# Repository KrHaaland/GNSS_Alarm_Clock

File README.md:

# GNSS Alarm Clock — Firmware

Firmware for the custom **SAMD51** alarm-clock board (Adafruit Metro M4
compatible), designed in `HARDWARE/` (KiCad). Two board revisions share one
firmware:

- **v2 (current)** — SAMD51J20A, **nPM1300 PMIC** with Li-ion charging and
  USB-C, LM3671 3.3 V + TPS61023 5 V boost, battery-backed RTC, MCU core on
  its internal buck regulator. See
  [`HARDWARE_V2.md`](HARDWARE_V2.md) and [ADR-0014](docs/adr/0014-npm1300-power-management.md)/[0015](docs/adr/0015-j20-default-swd-flashing.md).
  Default build: `metro_m4_j20`.
- **v1 (prototype)** — SAMD51J19A, LTC3226 + supercaps (design in
  `HARDWARE_OLD/`). Build: `adafruit_metro_m4`. The firmware detects the
  PMIC at runtime and degrades gracefully either way.

Time is set automatically from GNSS, the timezone (with DST) is derived offline
from the GNSS coordinates and saved to flash so it stays correct indoors, and
alarms drive an LED light-show + a tune through a class-D amp. The UI is LVGL on
a 428×142 color TFT driven by four buttons.

> **Current state:** firmware is feature-complete and running on hardware —
> display, GNSS time/timezone, alarms, audio, tunes-over-USB, settings, modes
> (speedometer/altimeter/USB-gamepad) and the RV-3028 RTC (hand-fitted; it was
> missing from the prototype) all work. See [`STATUS.md`](STATUS.md) and
> [`HARDWARE_REVIEW.md`](HARDWARE_REVIEW.md).

## Documentation

- **[User guide](docs/USER_GUIDE.md)** — buttons, menu, alarms, modes, tunes
- **[Architecture decisions](docs/adr/)** — why things are the way they are
- **[STATUS.md](STATUS.md)** — living status report · **[HARDWARE_REVIEW.md](HARDWARE_REVIEW.md)** — board findings
- **[HARDWARE_V2.md](HARDWARE_V2.md)** — v2 board reference (pinout, power tree, gotchas) · **[docs/sessions/](docs/sessions/)** — bench-session logs
- CI: GitHub Actions builds all firmware targets + runs the native test suite on every push

## What it does

- **Time**: The Quectel **L86** GNSS receiver (Serial1, 9600 NMEA, RMC+GGA @1 Hz
  plus GSV satellites-in-view every 5 s for the Sky-view screen, TinyGPS++ +
  a small in-house GSV parser) provides UTC. The clock is a `millis()`-anchored UTC counter
  disciplined by GNSS (re-syncs hourly / on ≥2 s drift) and backed by the
  **RV-3028-C7** RTC (I²C 0x52), whose VBACKUP sits on the battery (v2; the
  v1 prototype used the supercap rail) so it holds time through power loss. On boot the clock starts from the RTC
  immediately and refines from GNSS when a fix is available. A cold-start guard
  rejects the L86's free-running "year-2080" date so garbage can't be written
  into the backup RTC.
- **Timezone from coordinates**: An embedded **offline** lookup (213-box table
  covering every UTC zone worldwide — multi-zone countries split by region, plus
  no-DST exceptions like Arizona / Saskatchewan / Queensland / Kaliningrad;
  borders like US-zones and Afghanistan/Pakistan/India aligned to the real
  meridians). **Polygon zones** are checked before the boxes: real IANA
  timezone borders generated from timezone-boundary-builder data by
  `tools/gen_tz_polys.py` (tunable resolution/flash budget; enclaves ordered
  first), refinable by hand in `tools/tz_polygon_editor.html` (map GUI:
  draw/edit vertices, probe a point, export the header). Two resolutions,
  picked by flash size: v2/J20 gets the fine map
  (`src/TimezonePolyDataFine.h`, ~1–2 km borders, 404 zones / 56k vertices,
  ~250 KB), v1/J19 the coarse one (`src/TimezonePolyData.h`, ~57 KB). Anything not inside a polygon or box falls back
  to a whole-hour longitude estimate, so **every coordinate resolves**. Maps
  the GNSS position to a
  **POSIX TZ string with DST rules** (e.g. Oslo →
  `CET-1CEST,M3.5.0,M10.5.0/3`). The result is **persisted to internal flash**,
  so local time (including DST changes) stays correct after reboot even with no
  fix indoors. A DST-aware POSIX evaluator (`Timezone.*`, host-unit-tested)
  computes the offset. Manual zone override is available in the menu.
- **Alarms**: Two independent alarms with per-weekday masks. On trigger:
  - the **34 LEDs** (3 sections: left 10 / bottom 14 / right 10) run a chase at
    full brightness from a battery-capable rail (v2: TPS61023 5 V boost;
    v1: the LTC3226 supercap rail) — brightness never depends on the USB
    supply. The light show is **switchable per alarm** (Lights in the alarm
    editor; off = sound-only alarm),
  - a tune plays: a **WAV** from the QSPI flash drive, or one of 3 built-in
    melodies, via **DAC0 → TPA2016D2** class-D amp → speaker. WAVs pass a
    **200 Hz high-pass** in firmware: sub-bass cost the most battery current
    (speaker impedance minimum) for the least sound (ADR-0010),
  - optional **escalation**: after *N* minutes unacknowledged, the power buzzer
    joins in (v1 hardware only — v2 dropped the buzzer); auto-silence after
    30 min.
  - **Snooze**: short-press any button, or double-tap the clock (LIS3DH).
    **Stop**: long-press any button.
- **UI**: **LVGL 9.5** on an **NV3007 color TFT** (see below), driven by the 4
  buttons above the display: `[Back/Menu] [Prev/–] [Next/+] [OK]`. Screens:
  clock, menu, alarm-edit, time & zone, display, tunes, system-info,
  **sky view** (GSV polar plot + SNR bars — indoor antenna-placement aid),
  ringing. A true-black theme keeps the panel dark. Optional **starry night**:
  twinkling stars behind the clock digits between 22:00 and 06:00.
- **Modes** (Menu → Mode, cycles in place; alarms keep working in all of them):
  - **Alarm clock** — the normal HH:MM face.
  - **Speedometer** — the big figure shows GNSS ground speed in **km/h**.
  - **Altimeter** — GNSS altitude in **m** (MSL).
  - **Game mode** — the LIS3DH becomes a **USB HID gamepad**: tilt = stick
    X/Y, B2–B4 = buttons 1–3 (B1 keeps its menu role). The HID interface is
    always in the descriptor; it only sends reports in this mode.
- **Power (v2)**: the nPM1300 is driven end-to-end — input limit follows the
  USB-C CC advertisement (500 mA on PC ports, 1500 mA on real chargers,
  re-applied instantly on replug via the PMIC's IRQ line on PA04), charging
  400/800 mA to 4.10 V under an 80/70 °C die thermostat, live battery
  current on the Battery screen, a drawn SoC gauge on the clock face
  (ADR-0014/0016), and a low-battery policy: ship mode below 3.40 V (never
  during an alarm), fullscreen LOW BATTERY on a too-early wake, manual
  Shutdown in the menu — BUTTON1 or USB wakes it, the RTC keeps time
  throughout. The volume ceiling is bench-tuned to the PMIC's **1000 mA
  battery discharge limit (IBATLIM)** — exceeding it collapses VSYS and
  resets the device, so max volume (+7 dBV limiter) + LED chase stays under
  it with margin (ADR-0010/0014).
- **Tune upload**: the QSPI flash appears as a **USB flash drive** (`TUNES`) —
  drag & drop `.wav` files (PCM, 8/16-bit, mono/stereo, 8–48 kHz).

## Screenshots

Grabbed from the live firmware over USB serial (`tools/screenshot.py`).

| | |
|---|---|
|  |  |
| Clock face — battery gauge, charge bolt, alarm bell | Starry night (22:00–06:00) |
|  |  |
| First boot, no RTC/GNSS time yet | Sky view — GSV polar plot + SNR bars |
|  |  |
| Main menu | …scrolled |
|  |  |
| Speedometer mode (GNSS) | Altimeter mode (GNSS) |
|  |  |
| Game mode — USB HID gamepad | The 3D-printed enclosure |

## Display (NV3007)

The panel is an **NV3007 color TFT** (Newvision), native 142×428 bar type,
driven **landscape 428×142**. Driver: [`src/DisplayNV3007.cpp`](src/DisplayNV3007.cpp).
(The v1 prototype's ST7789 284×76 driver is kept in-tree — pick the panel via
**DISPLAY SELECT** in `platformio.ini`.)

- **Vendor init is mandatory**: `0xFF 0xA5` unlocks the extended register page
  (power/gamma/gate-driver/source-timing dump); without it the address engine
  wraps writes linearly across the glass. `0xFF 0x00` returns to the DCS page.
  Sequence cross-verified against five independent drivers (Arduino_GFX, LVGL
  lv_nv3007, vendor reference, STM32 + esp_lcd ports).
- GRAM is **168×428**; the 142 visible columns are inset 12/14. Landscape
  (`MADCTL 0xA0`, flipped 180° to match the enclosure mounting) puts the
  inset on RASET: **`NV_Y_OFFSET 12`** (unflipped 0x60 → 14). Inversion OFF.
- **SPI mode 0** (an NV3007 quirk — ST7789 setups often run mode 3), **30 MHz**
  (SERCOM2 re-clocked from the 120 MHz GCLK0 — the default 48 MHz source
  quantizes to 24 MHz max). Pixels stream via an **async DMA flush with double
  buffering** (ADR-0012, superseding ADR-0002's DMA ban): LVGL renders the
  next strip while the DMAC streams the previous one, and the completion IRQ
  hands the buffer back. Falls back to a synchronous DRE-paced register loop
  if the DMA channel is unavailable. Full frame ~26 ms on the wire, hidden
  behind rendering.
- Known silicon quirk: tiny partial writes can half-light adjacent pixels for
  RGB channel values 1–31 against black; LVGL's strip-sized flushes avoid it.
- Backlight D11/PA19, PWM-dimmed; shake-to-wake; `DISPLAY_SELFTEST` bring-up
  pattern test (colors/border/origin) as before.
- The clock figure uses a **generated 100 px Montserrat subset**
  (`src/font_clock_100.c`, 18 chars) — replacing the full 48 px font actually
  **shrank** flash by 67 KB (ADR-0011).

## Storage decision

The board has two candidate "EEPROMs" for tunes: the 24LC512 (64 KB, I²C) and a
QSPI serial flash. The firmware uses the **QSPI flash** (exposed as the USB
drive): far larger, faster, on the standard Metro M4 QSPI pins, and it enables
the drag-and-drop workflow.

**Settings** are packed into the **RV-3028 RTC's 43-byte user EEPROM**.
Chosen because it survives **firmware reflashes** (the old internal-flash
emulation sat inside the app image and was wiped on every update), takes
~100k writes/byte, and frees the **24LC512 to be dropped from the hardware-v2
BOM** (it still ACKs at 0x50 on v1 boards, unused). Verified on hardware:
settings survive both power cycles and reflashes.

### RTC user-EEPROM memory map (38 of 43 bytes)

Space is won by not storing derived data: TZ strings re-derive at boot from
the stored position (or the manual GMT-ladder index), and alarm tune filenames
are stored as 16-bit FNV-1a hashes re-matched against the TUNES directory
(missing file → builtin melody). Multi-byte fields are little-endian.

| Addr | Size | Field |
|---|---|---|
| `0x00` | 2 | Magic `'G' 'C'` |
| `0x02` | 1 | Pack-format version (4) — older blocks (v1–v3) migrate in place at boot, nothing is reset |
| `0x03` | 1 | Flags: b0 tzAuto, b1 tapSnooze, b2 use24h, b3 havePosition, b4–5 mode, b6 starryNight |
| `0x04` | 2 | Latitude, centidegrees (i16) |
| `0x06` | 2 | Longitude, centidegrees (i16) |
| `0x08` | 1 | Manual zone index into `TZ_TABLE` (`0xFF` = none/auto) |
| `0x09` | 1 | Volume (0–10) |
| `0x0A` | 1 | Snooze minutes |
| `0x0B` | 1 | Buzzer escalation after N min (0 = off) |
| `0x0C` | 1 | Brightness |
| `0x0D` | 2 | Dim timeout, seconds (u16) |
| `0x0F` | 1 | Dim brightness |
| `0x10` | 3 | Snooze counter, all time (u24, caps at 16.7 M) |
| `0x13` | 2 | Snooze counter, this week (u16) |
| `0x15` | 2 | Week start, local epoch-day − 18262 (u16, base 2020-01-01) |
| `0x17` | 7 | Alarm 1: flags (b0 enabled, b1–2 ramp Off/15/30/60 s, b3–4 random ±0/1/5/9 min, b5 lights-OFF — inverted so old blocks read as on), hour, minute, daysMask, melodyId, tuneHash (u16) |
| `0x1E` | 7 | Alarm 2: same layout |
| `0x25` | 1 | Checksum (block sums to `0xFF`) — **written last**, so a torn write invalidates the image |
| `0x26` | 5 | Free / future |

> **RV-3028 EEPROM quirks (bench-found, handled in `RtcRV3028.cpp`):** the
> chip **NACKs all I²C** while its EEPROM engine runs — both during the
> power-on auto-refresh (>100 ms) and in short windows after each programmed
> byte. The driver therefore treats failed STATUS reads as "still busy"
> (300 ms deadline), retries each byte transaction up to 5×, and read-back
> verifies every written byte.

> **Flash BOM note:** the schematic specifies a 4 MB Macronix MX25L3233F, but
> assembled boards carry a **16 MB Winbond W25Q128** (JEDEC 0xEF4018). The driver
> auto-detects the real chip via the library's default device list, so the true
> size is used for the USB drive.

## Pin map (from the KiCad netlist)

| Function | MCU pin | Arduino pin |
|---|---|---|
| Display CS / DC / RST / BL | PA18 / PA17 / PA16 / PA19 | D10 / D12 / D13 / D11 |
| Display SPI (SERCOM2) | PA12 MOSI, PA13 SCK | MOSI/SCK |
| GNSS L86 UART (SERCOM3) | PA22 TX → L86, PA23 RX ← L86 | Serial1 |
| GNSS FORCE_ON / RESET_N | PB00 / PB31 | direct port |
| I²C @100 kHz: RTC 0x52, amp 0x58, accel 0x18, EEPROM 0x50 | PB02 SDA, PB03 SCL | SDA/SCL |
| Buttons SW1..SW4 (L→R, active low) | PB14, PB13, PB12, PB15 | D5, D4, D7, D6 |
| LED gates: left / bottom / right | PA21 / PA20 / PA06 | D8 / D9 / A2 |
| Audio DAC → TPA2016 | PA02 (DAC0) | A0 |
| Amp ~SD (HIGH = on) | PB17 | D2 |
| Power buzzer gate (J5) | PB16 | D3 |
| Supercap CAPGOOD (LTC3226) | PA04 | A3 |
| LIS3DH INT1 (polled, unused) | PB08 | A4 |
| 24LC512 WP | PB01 | direct port |
| QSPI flash | PA08–11, PB10, PB11 | QSPI |

## Building & flashing

```sh
pio run                      # build (default env: adafruit_metro_m4)
pio test -e native           # host-side unit tests (timezone/DST engine)
```

### MCU select (J19 / J20)

The prototype has a **SAMD51J19A** (512 KB flash, ~95% full); the next revision
uses a **SAMD51J20A** (1 MB flash, ~48% — same pinout). Pick the build in
`platformio.ini` (`default_envs`) or per-invocation:

| env | MCU | notes |
|---|---|---|
| `adafruit_metro_m4` | J19A 512 KB | default (current prototype) |
| `metro_m4_j20` | J20A 1 MB | `boards/samd51j20a_metro.json` + `ld/samd51j20a_*.ld` |
| `sim` / `sim_j20` | either | + serial GNSS simulator (`-DGNSS_SIM`) |

```sh
pio run -e metro_m4_j20      # J20 build; flash .pio/build/metro_m4_j20/firmware.bin @0x4000
```

> **J20 + stock bootloader:** the Metro M4 UF2 bootloader is built for the
> J19A and reads the "stay in bootloader" magic at *its* RAM top
> (0x2002FFFC); a J20 app writes it at 0x2003FFFC, so the 1200-baud touch
> used to land straight back in the app. `tools/patch_tinyusb_power.py`
> patches the core's `initiateReset()` to write **both** addresses — USB
> uploads now work on the J20 with the stock bootloader.

Two flashing paths:

**A) USB (normal, no tools):** `pio run -e metro_m4_j20 -t upload` —
1200-baud touch into the bootloader, bossac writes + verifies at 0x4000
(~4 s). Manual alternative: double-tap RESET to mount the `METROM4BOOT`
drive and drag `firmware.uf2` onto it.

**B) SWD via Atmel-ICE (used in development):**

```sh
# build first, then flash the .bin at 0x4000 (offset preserves the bootloader)
openocd -c "adapter driver cmsis-dap" -c "transport select swd" \
        -c "adapter speed 2000" -f target/atsame5x.cfg \
        -c "init" -c "reset halt" \
        -c "flash write_image erase .pio/build/adafruit_metro_m4/firmware.bin 0x00004000 bin" \
        -c "reset run" -c "shutdown"
```

> ⚠️ **Never flash the `.elf` over SWD.** Its LOAD segment sits at address `0x0`
> and will overwrite the UF2 bootloader at flash start, bricking drag-and-drop
> programming (recovery = re-flash the bootloader). Always flash the **`.bin` at
> `0x4000`**. The bootloader region is additionally guarded by the
> **BOOTPROT fuse (16 KB)** since a brownout-induced wild NVMCTRL write once
> zeroed the bootloader's vector table (see `docs/sessions/`); clear it with
> `atsame5 bootloader 0` before intentional bootloader updates, restore with
> `atsame5 bootloader 16384`.

`pio device monitor -b 115200` opens the USB-CDC console. Sending `~` on
the console streams the next rendered frame as a screenshot —
`python3 tools/screenshot.py` grabs it and writes a PNG (used for the
documentation images; works on the live device, any screen).

### USB identity

The app enumerates as **`1209:0001` — "K. Haaland / GNSS Alarm Clock"**.
VID `0x1209` belongs to [pid.codes](https://pid.codes) (free USB IDs for
open-source hardware); `0x0001` is their official **test PID**, fine for
personal use — register a permanent PID via a pid.codes PR (requires a public,
OSI-licensed repo) before distributing hardware. Identity lives in
`boards/samd51j19a_kh.json` / `boards/samd51j20a_metro.json`. Bootloader mode
(double-tap reset) still enumerates as Adafruit `239A` until a custom
uf2-samdx1 is built.

### Simulated GNSS (`env:sim`)

To test the timezone/clock pipeline on-device **without a real fix**, build the
`sim` env — identical firmware plus `-DGNSS_SIM` (the L86 init is skipped and a
serial console feeds position/time):

```sh
pio run -e sim -t upload      # or SWD-flash .pio/build/sim/firmware.bin @0x4000
pio device monitor -b 115200
```

Then type commands into the monitor:

```
pos 59.91 10.75              set a fix; resolves + applies the timezone
tz  -33.87 151.2             query a zone (Jan/Jul offset + DST), no state change
utc 2026 7 13 12 0 0         set the UTC clock so local time shows on the display
status                       print fix / UTC / local time / zone
nofix                        drop the simulated fix
```

`pos` also updates the on-screen clock's zone immediately, so you can watch the
display follow you around the globe. The `sim` code compiles to nothing in the
normal build — zero production-flash cost.

## Source layout

| File | Responsibility |
|---|---|
| `src/main.cpp` | Boot order, super-loop, alarm ↔ UI ↔ button routing, I²C @100 kHz |
| `src/ClockKeeper.*` | UTC anchor, GNSS→RTC discipline, local time / DST |
| `src/Timezone.*` | Coord→zone polygons+boxes + POSIX TZ/DST evaluator (host-testable) |
| `src/TimezonePolyData.h` | Polygon zone data: `tools/gen_tz_polys.py` (world set) / `tools/tz_polygon_editor.html` (hand edits) |
| `src/Gnss.*` | L86 NMEA via TinyGPS++, PMTK config, position/speed/altitude |
| `src/RtcRV3028.*` | RV-3028-C7 driver wrapper (backup switchover, UTC, PORF) |
| `src/AlarmManager.*` | Trigger scan, ringing/snooze/escalation state machine |
| `src/AudioEngine.*` | TC2 ISR → DAC0 playback, WAV streaming, melodies, buzzer |
| `src/TuneStorage.*` | QSPI flash, FAT12 volume, USB mass storage |
| `src/DisplayST7789.*` | ST7789 driver + LVGL 9 flush (RGB565), bring-up self-test |
| `src/Ui.*` | LVGL screens: clock, menu, alarm edit, zone, display, tunes, info, sky view, battery, lights, ringing |
| `src/PmicNPM1300.*` | nPM1300: CC-based input limit, charger, IBAT/SoC, ship mode, IRQ (v2) |
| `src/Buttons.*` / `src/Leds.*` | Debounced input, LED section patterns |
| `src/AmpTPA2016.*` / `src/AccelLIS3DH.*` | Amp gain/enable, double-tap-to-snooze |
| `src/Settings.*` | Persistent settings packed into the RTC's user EEPROM (v4, 38 B) |
| `src/SimConsole.*` | Serial "virtual GPS" console — `env:sim` only (`-DGNSS_SIM`) |

## Diagnostics (compile-time, default off)

- `DISPLAY_SELFTEST` in [`DisplayST7789.cpp`](src/DisplayST7789.cpp) — on-glass
  pattern test (RGB fills, edge border) instead of LVGL.
- `I2C_SCAN` in [`main.cpp`](src/main.cpp) — loops scanning the I²C bus and
  prints ACKing addresses over USB serial (used to diagnose the RTC).

## Known issues / verify on hardware

See [`STATUS.md`](STATUS.md) for the full list. Highlights:

- 🔴 **RV-3028 RTC (U5) does not ACK on I²C** — bad joint / power on U5; being
  reflowed. (Time still works from GNSS; only power-off holdover is affected.)
- **L86 1PPS (pin 6) and AADET_N (pin 8) are unrouted** — no hardware PPS
  timing, no antenna-detect.
- **`CAPGOOD` polarity** assumed HIGH = charged (LTC3226 open-drain + pullup).
- Plus the schematic findings in [`HARDWARE_REVIEW.md`](HARDWARE_REVIEW.md)
  (LM3671 VIN/SW, L86 V_BCKP cold-start, D3 diode, C30, crystal caps, …).

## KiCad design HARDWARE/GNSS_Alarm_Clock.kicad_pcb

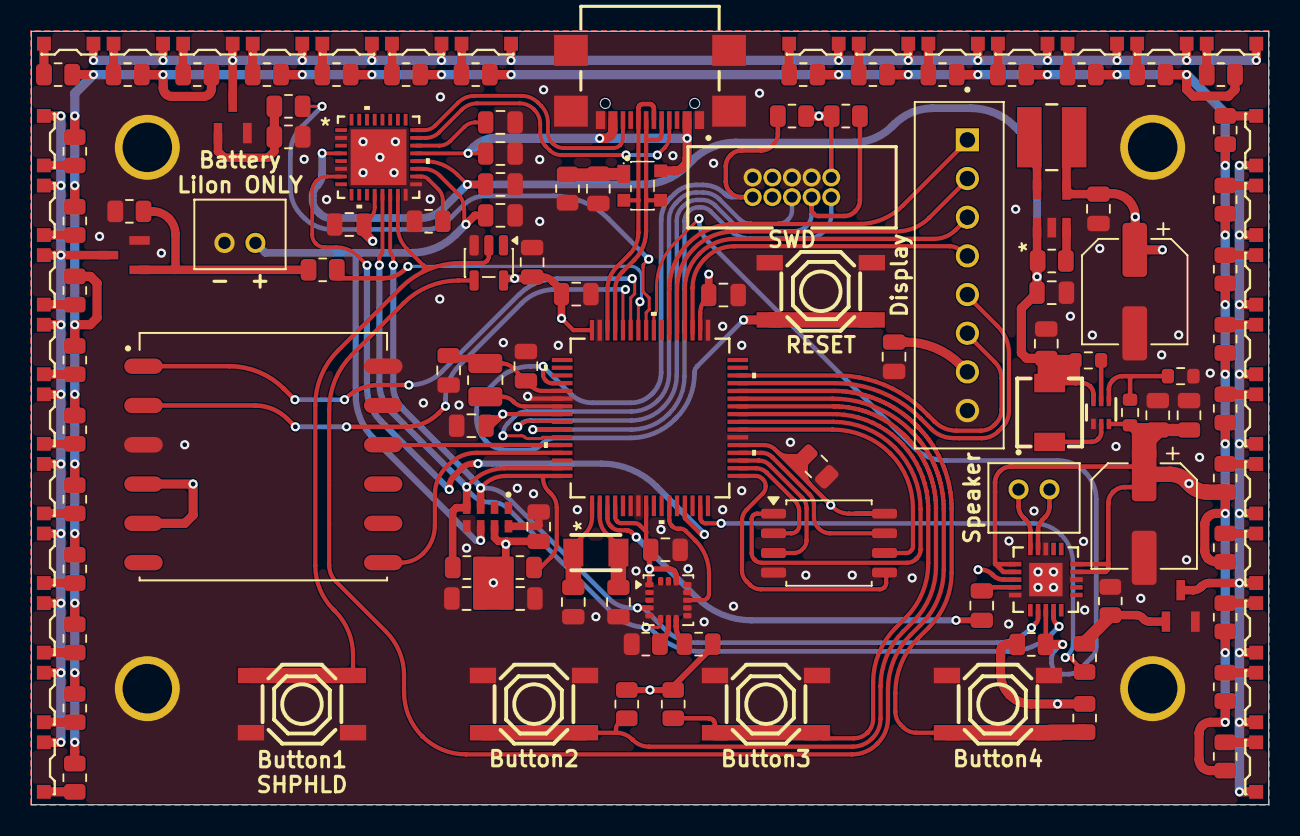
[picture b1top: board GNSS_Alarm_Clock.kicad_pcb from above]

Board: 4 copper layers, 80.0 x 50.0 mm, 146 parts (0 on the bottom side), 101 nets.

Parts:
C1, C3, C4: 22µF; C_0805_2012Metric
C2, C5, C26: 1uF; C_0805_2012Metric
C6, C7, C8, C9, C10, C11, C12, C16, C17, C19, C20, C22, C28: 10uF; C_0805_2012Metric
C13: 4.7uF; C_0805_2012Metric
C14, C15, C27: 100nF; C_0805_2012Metric
C18, C21: 220uF; CP_Elec_6.3x5.7
C24, C25: 10pF; C_0805_2012Metric
C29: 10μF; C_0805_2012Metric
J1: USB4110GFA; USB4110-GF-A
J3: SWD-Connector_3220-10-0100-00; SWD-Connector
J4: B8B-XH-A
J6, J7: B2B-PH-K-S
L1: 2.2uH; VLCF4020T-2R2N1R7
L2: 1µH; YXMAA0412-1R0M-ANP
L4: 10uH; L_1008_2520Metric
LED1, LED2, LED3, LED4, LED5, LED6, LED7, LED8, LED9, LED10, LED11, LED12, LED13, LED14, LED15, LED16, LED17, LED18, LED19, LED20, LED21, LED22, LED23, LED24, LED25, LED26, LED27, LED28, LED29, LED30, LED31, LED32, LED33, LED34: OR-PL020W
R1, R8, R9, R10: 1M; R_0805_2012Metric
R4, R12: 100KΩ; R_0603_1608Metric
R5: 732KΩ; R_0603_1608Metric
R6, R7: 4.7K; R_0805_2012Metric
R13: 100k; R_0805_2012Metric
R15, R54, R56: 470Ω; R_0805_2012Metric
R16: 10KΩ; R_0805_2012Metric
R18, R55, R57, R58, R63, R68: 10kΩ; R_0805_2012Metric
R20, R21, R22, R23, R24, R25, R26, R27, R28, R29, R30, R31, R32, R33, R34, R35, R36, R37, R38, R39, R40, R41, R42, R43, R44, R45, R46, R47, R48, R49, R50, R51, R52, R53: 80Ω; R_0805_2012Metric
R66: 1kΩ; R_0805_2012Metric
R67: 100kΩ; R_0805_2012Metric
SW1, SW2, SW3, SW4, SW5: TS-1187A-B-A-B
U1: TPA2016D2RTJR; TPA2016D2
U2: PRTR5V0U2X_C2827688; PRTR5V0U2X
U3: NPM1300-QEAA-R7; nPM1300
U4: L86-M33
U5: RV-3028-C7
U6: TPS61023DRLR; TPS61023
U7: LIS3DH; LGA-16_3x3mm_P0.5mm_LayoutBorder3x5y
U8: 25Q128; SOIC-8_5.3x5.3mm_P1.27mm
U9: 74LVC1G17; SOT-23-5
U10, U11, U12: IRLML6344TRPBF; IRLML6344
U14: LM3671MFX-3.3/NOPB; LM3671MFX-3.3
U18: ATSAMD51J19A-AUT; ATSAMD51J19_TQFP
X1: 32.768; Q13FC13500005

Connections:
+3.3V: C6.1, C7.1, C8.1, C9.1, C10.1, C11.1, C14.1, C15.1, C16.1, C17.1, C18.1, C20.1, C28.1, J3.1 (Vref), J4.7, L1.2, R6.2, R7.2, R8.1, R9.1, R10.1, R63.1, R66.2, R67.2, R68.2, U1.13 (AVDD), U3.12 (VDDIO), U4.4 (VCC), U4.5 (V_BCKP), U5.7 (VDD), U7.1 (VDD_IO), U7.14 (VDD), U8.8 (VCC), U9.5 (VCC), U14.4 (FB), U18.4 (PA03), U18.8 (VDDANA), U18.21 (VDDIOB), U18.34 (VDDIO), U18.48 (VDDIO), U18.56 (VDDIO)
+5V: C1.1, C4.1, C21.1, R5.1, R20.1, R21.1, R22.1, R23.1, R24.1, R25.1, R26.1, R27.1, R28.1, R29.1, R30.1, R31.1, R32.1, R33.1, R34.1, R35.1, R36.1, R37.1, R38.1, R39.1, R40.1, R41.1, R42.1, R43.1, R44.1, R45.1, R46.1, R47.1, R48.1, R49.1, R50.1, R51.1, R52.1, R53.1, U1.4 (PVDDL_2), U1.5 (PVDDL), U1.11 (PVDDR_2), U1.12 (PVDDR), U6.6 (VOUT)
AmpShutdown: R68.1, U1.18 (SDZ), U18.40 (D2/PB17)
Analog: C27.1, U18.3 (PA02/A0/PWM)
BUTTON1: U9.4, U18.27 (PB14/D5)
BUTTON2: R8.2, SW2.3, SW2.4, U18.26 (PB13/D4)
BUTTON3: R9.2, SW3.3, SW3.4, U18.25 (PB12/D7)
BUTTON4: R10.2, SW4.3, SW4.4, U18.28 (PB15/D6)
DISP_BL: J4.1, U18.38 (D11/PA19)
DISP_CS: J4.2, U18.37 (D10/PA18)
DISP_DC: J4.3, U18.36 (D12/PA17)
DISP_RST: J4.4, U18.35 (D13/PA16)
GND: C1.2, C2.2, C3.2, C4.2, C5.2, C6.2, C7.2, C8.2, C9.2, C10.2, C11.2, C12.2, C13.1, C14.2, C15.2, C16.2, C17.2, C18.2, C19.2, C20.2, C21.2, C22.2, C24.1, C25.1, C26.1, C28.2, C29.1, J1.A1/B12 (GND), J1.B1/A12 (GND__1), J1.S1 (GND__2), J1.S2 (GND__3), J1.S3 (GND__4), J1.S4 (GND__5), J3.3 (GND), J3.5 (GND), J3.9 (GND), J4.8, J7.2, R1.2, R12.2, R16.1, R18.1, R55.2, R57.2, R58.2, SW1.3, SW1.4, SW2.1, SW2.2, SW3.1, SW3.2, SW4.1, SW4.2, SW5.3, SW5.4, U1.3 (AGND), U1.8 (PGND), U1.15 (INR+), U1.21 (EP), U3.2 (PVSS1), U3.6 (PVSS2), U3.16 (VSET2), U3.17 (VSET1), U3.33 (AVSS), U4.3 (GND), U4.12 (GND), U5.5 (VSS), U5.8 (EVI), U6.4 (GND), U7.5 (GND), U7.10 (GND), U7.12 (GND), U8.4 (GND), U9.3 (GND), U10.2, U11.2, U12.2, U14.2 (GND), U18.7 (GNDANA), U18.22 (GND), U18.33 (GND), U18.47 (GND), U18.54 (GND)
GNSS_FOn: U4.7 (FORCE_ON), U18.61 (PB00)
GNSS_Reset: U4.10 (~RESET), U18.60 (PB31)
I2C_SCL: R7.1, U1.17 (SCL), U3.14 (SCL), U5.3 (SCL), U7.4 (SCL/SPC), U18.64 (SCL/PB03)
I2C_SDA: R6.1, U1.19 (SDA), U3.13 (SDA), U5.4 (SDA), U7.6 (SDA/SDI/SDO), U18.63 (SDA/PB02)
LIS3DH_INT1: U7.11 (INT1), U18.11 (PB08/A4)
LedsB-K: LED11.1 (-), LED12.1 (-), LED13.1 (-), LED14.1 (-), LED15.1 (-), LED16.1 (-), LED17.1 (-), LED18.1 (-), LED19.1 (-), LED20.1 (-), LED21.1 (-), LED22.1 (-), LED23.1 (-), LED24.1 (-), U11.3
LedsB-S: R54.1, U18.41 (D9/PA20)
LedsL-K: LED1.1 (-), LED2.1 (-), LED3.1 (-), LED4.1 (-), LED5.1 (-), LED6.1 (-), LED7.1 (-), LED8.1 (-), LED9.1 (-), LED10.1 (-), U10.3
LedsL-S: R15.1, U18.42 (D8/PA21)
LedsR-K: LED25.1 (-), LED26.1 (-), LED27.1 (-), LED28.1 (-), LED29.1 (-), LED30.1 (-), LED31.1 (-), LED32.1 (-), LED33.1 (-), LED34.1 (-), U12.3
LedsR-S: R56.1, U18.15 (PA06/A2)
McuRX: U4.2 (TXD1), U18.44 (RX/D0/PA23)
McuTX: U4.1 (RXD1), U18.43 (TX/D1/PA22)
unnamed: C2.1, R1.1, U2.1
unnamed: LED1.2 (+), R20.2
unnamed: LED2.2 (+), R21.2
unnamed: LED3.2 (+), R22.2
unnamed: LED4.2 (+), R23.2
unnamed: LED5.2 (+), R24.2
unnamed: LED6.2 (+), R25.2
unnamed: LED7.2 (+), R26.2
unnamed: LED8.2 (+), R27.2
unnamed: LED9.2 (+), R28.2
unnamed: LED10.2 (+), R29.2
unnamed: LED11.2 (+), R30.2
unnamed: LED12.2 (+), R31.2
unnamed: LED13.2 (+), R32.2
unnamed: LED14.2 (+), R33.2
unnamed: LED15.2 (+), R34.2
unnamed: LED16.2 (+), R35.2
unnamed: LED17.2 (+), R36.2
unnamed: LED18.2 (+), R37.2
unnamed: LED19.2 (+), R38.2
unnamed: LED20.2 (+), R39.2
unnamed: LED21.2 (+), R40.2
unnamed: LED22.2 (+), R41.2
unnamed: LED23.2 (+), R42.2
unnamed: LED24.2 (+), R43.2
unnamed: LED25.2 (+), R44.2
unnamed: LED26.2 (+), R45.2
unnamed: LED27.2 (+), R46.2
unnamed: LED28.2 (+), R47.2
unnamed: LED29.2 (+), R48.2
unnamed: LED30.2 (+), R49.2
unnamed: LED31.2 (+), R50.2
unnamed: LED32.2 (+), R51.2
unnamed: LED33.2 (+), R52.2
unnamed: LED34.2 (+), R53.2
unnamed: R15.2, R57.1, U10.1
unnamed: R54.2, R55.1, U11.1
unnamed: R56.2, R58.1, U12.1
unnamed: C27.2, U1.14 (INR-)
unnamed: J6.1, U1.10 (OUTR+)
unnamed: J6.2, U1.9 (OUTR-)
unnamed: R16.2, U3.18 (NTC)
unnamed: SW1.1, SW1.2, U3.15 (SHPHLD), U9.2
unnamed: C5.1, U3.22 (VBUSOUT)
unnamed: R4.2, U6.2 (EN)
unnamed: R5.2, R12.1, U6.1 (FB)
unnamed: L2.2, U6.5 (SW)
unnamed: R63.2, U7.8 (CS)
unnamed: R18.2, U7.7 (SDO/SA0)
unnamed: R13.1, U14.3 (EN)
unnamed: L1.1, U14.5 (SW)
unnamed: C24.2, U18.1 (PA00), X1.2
unnamed: C25.2, U18.2 (PA01), X1.1
unnamed: U8.5 (SI/SIO0), U18.17 (PA08/FlashIO0)
unnamed: U8.2 (SO/SIO1), U18.18 (PA09/FlashIO1)
unnamed: U8.3 (~WP/SIO2), U18.19 (PA10/FlashIO2)
unnamed: U8.7 (~HOLD/SIO3), U18.20 (PA11/FlashIO3)
unnamed: U8.6 (SCLK), U18.23 (PB10/FlashSCK)
unnamed: U8.1 (~CS), U18.24 (PB11/FlashCS)
unnamed: C26.2, C29.2, L4.1, U18.53 (VDDCORE)
unnamed: L4.2, U18.55 (VSW)
PMIC_GPIO0: U3.7 (GPIO0), U18.13 (PA04/A3)
SPI_MOSI: J4.5, U18.29 (PA12/MOSI)
SPI_SCK: J4.6, U18.30 (PA13/SCK)
SWD_CLK: J3.4 (SWD_CLK), R66.1, U18.57 (SWDCLK/PA30)
SWD_IO: J3.2 (SWD_IO), U18.58 (SWDIO/PA31)
SWD_RST: J3.10 (SWD_RST), R67.1, SW5.1, SW5.2, U18.52 (RESETN)
SWO: J3.6 (SWO/TDO), U18.59 (SWO/PB30)
USB_CC1: J1.A5 (CC1), U3.23 (CC1)
USB_CC2: J1.B5 (CC2), U3.24 (CC2)
USB_N: J1.A7 (DN1), J1.B7 (DN2), U2.3, U18.45 (USB-D-/PA24)
USB_P: J1.A6 (DP1), J1.B6 (DP2), U2.2, U18.46 (USB-D+/PA25)
VBAT: C13.2, J7.1, U3.19 (VBAT), U5.6 (VBACKUP)
VSYS: C3.1, C19.1, C22.1, L2.1, R4.1, R13.2, U3.4 (PVDD), U3.20 (VSYS), U6.3 (VIN), U14.1 (VIN)
VUSB: C12.1, J1.A4/B9 (VBUS), J1.B4/A9 (VBUS__1), U2.4, U3.21 (VBUS)

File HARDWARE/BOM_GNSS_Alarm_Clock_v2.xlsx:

GNSS Alarm Clock v2 - Bill of Materials
Generated from HARDWARE/GNSS_Alarm_Clock.kicad_pcb, 2026-08-10. 146 components,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
Designators | Qty | Value / Part | Footprint | Library | Notes
C1, C3, C4 | 3 | 22uF | C_0805_2012Metric | Capacitor_SMD
C2, C5, C26 | 3 | 1uF | C_0805_2012Metric | Capacitor_SMD
C6, C7, C8, C9, C10, C11, C12, C16, C17, C19, C20, C22, C28, C29 | 14 | 10uF | C_0805_2012Metric | Capacitor_SMD
C13 | 1 | 4.7uF | C_0805_2012Metric | Capacitor_SMD
C14, C15, C27 | 3 | 100nF | C_0805_2012Metric | Capacitor_SMD
C18, C21 | 2 | 220uF | CP_Elec_6.3x5.7 | Capacitor_SMD | Bulk electrolytic - polymer upgrade candidate (e.g. Nichicon RSA series), 10V r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
C24, C25 | 2 | 10pF | C_0805_2012Metric | Capacitor_SMD
J1 | 1 | USB4110GFA | USB4110-GF-A | Kicad8_multilib
J3 | 1 | SWD-Connector_3220-10-0100-00 | SWD-Connector | Kicad8_multilib
J4 | 1 | B8B-XH-A | B8B-XH-A | Kicad8_multilib
J6, J7 | 2 | B2B-PH-K-S | B2B-PH-K-S | Kicad8_multilib | Battery connector - production cell: 505060 LiPo 3.7V 2000mAh with PCM.
L1 | 1 | 2.2uH | VLCF4020T-2R2N1R7 | Kicad8_multilib
L2 | 1 | 1uH | YXMAA0412-1R0M-ANP | Kicad8_multilib
L4 | 1 | 10uH | L_1008_2520Metric | Inductor_SMD
LED1, LED2, LED3, LED4, LED5, LED6, LED7, LED8, LED9, LED10, LED11, LED12, LED1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 | 34 | OR-PL020W | OR-PL020W | Kicad8_multilib
R1, R8, R9, R10 | 4 | 1MΩ | R_0805_2012Metric | Resistor_SMD
R4, R12 | 2 | 100kΩ | R_0603_1608Metric | Resistor_SMD
R5 | 1 | 732kΩ | R_0603_1608Metric | Resistor_SMD
R6, R7 | 2 | 4.7kΩ | R_0805_2012Metric | Resistor_SMD
R13, R67 | 2 | 100kΩ | R_0805_2012Metric | Resistor_SMD
R15, R54, R56 | 3 | 470Ω | R_0805_2012Metric | Resistor_SMD
R16, R18, R55, R57, R58, R63, R68 | 7 | 10kΩ | R_0805_2012Metric | Resistor_SMD | v3 change queued: amp ~SD pull-up should become pull-DOWN (boot noise).
R20, R21, R22, R23, R24, R25, R26, R27, R28, R29, R30, R31, R32, R33, R34, R35,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 | 34 | 80Ω | R_0805_2012Metric | Resistor_SMD
R66 | 1 | 1kΩ | R_0805_2012Metric | Resistor_SMD
SW1, SW2, SW3, SW4, SW5 | 5 | TS-1187A-B-A-B | TS-1187A-B-A-B | Kicad8_multilib
U1 | 1 | TPA2016D2RTJR | TPA2016D2 | Kicad8_multilib
U2 | 1 | PRTR5V0U2X_C2827688 | PRTR5V0U2X | Kicad8_multilib
U3 | 1 | NPM1300-QEAA-R7 | nPM1300 | Kicad8_multilib
U4 | 1 | L86-M33 | L86-M33 | Kicad8_multilib
U5 | 1 | RV-3028-C7 | RV-3028-C7 | Kicad8_multilib
U6 | 1 | TPS61023DRLR | TPS61023 | Kicad8_multilib
U7 | 1 | LIS3DH | LGA-16_3x3mm_P0.5mm_LayoutBorder3x5y | Package_LGA
U8 | 1 | 25Q128 | SOIC-8_5.3x5.3mm_P1.27mm | Package_SO | Correct part: W25Q128JVSIQ (3.0V). A 1.8V W25Q128FW was fitted by mistake once;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
U9 | 1 | 74LVC1G17 | SOT-23-5 | Package_TO_SOT_SMD
U10, U11, U12 | 3 | IRLML6344TRPBF | IRLML6344 | Kicad8_multilib
U14 | 1 | LM3671MFX-3.3/NOPB | LM3671MFX-3.3 | Kicad8_multilib
U18 | 1 | ATSAMD51J19A-AUT | ATSAMD51J19_TQFP | Kicad8_multilib | Schematic says SAMD51J19A - FITTED PART IS SAMD51J20A (verified via bossac). Or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
X1 | 1 | 32.768 | Q13FC13500005 | Kicad8_multilib

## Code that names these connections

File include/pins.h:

// pins.h — Board pin map for the GNSS Alarm Clock (custom SAMD51 board,
// Adafruit Metro M4 compatible variant; v1 = J19A, v2 = J20A — pin-identical
// in TQFP64).
//
// Verified against the v2 KiCad design (HARDWARE/, see HARDWARE_V2.md for the
// full 64-pad reference) and cross-checked against HARDWARE_OLD/ (v1). The map
// is near-identical between v1 and v2; the v2-only differences are:
//   - PA04 = nPM1300 GPIO0 (was LTC3226 CAPGOOD; unconfigured reads LOW)
//   - PB16 unconnected (escalation buzzer removed)
//   - PB01 unconnected (24LC512 EEPROM removed)
//   - BUTTON1 (PB14) is driven by a 74LVC1G17 buffer (U9) whose input is the
//     PMIC SHPHLD pin, not a raw switch; the physical SW1 doubles as the
//     nPM1300 wake/reset. Same active-low polarity as v1 at the MCU.
// Arduino pin numbers are the adafruit_metro_m4 variant (verified against
// variant.cpp / variant.h). "direct port" = pin is NOT in that variant, so it
// needs raw PORT register access (see portb_*() helpers below).
//
//  SAMD51 pin | Net         | Arduino | Function
//  -----------+-------------+---------+---------------------------------------
//  PA02       | Analog      | 14/A0   | Audio out (DAC0) -> C27 -> TPA2016 INR-
//  PA04       | PMIC_GPIO0  | 17/A3   | nPM1300 GPIO0 (v1: LTC3226 CAPGOOD)
//  PA06       | LedsR-S     | 16/A2   | Right LED section gate -> 470R -> U12
//  PA12       | SPI_MOSI    | 26/MOSI | Display SPI MOSI (SERCOM2) -> J4.5
//  PA13       | SPI_SCK     | 25/SCK  | Display SPI SCK  (SERCOM2) -> J4.6
//  PA14       | SPI_MISO    | 24/MISO | SPI MISO (not routed to J4 panel)
//  PA16       | DISP_RST    | 13      | display reset (active low), J4.4
//  PA17       | DISP_DC     | 12      | display data/command, J4.3
//  PA18       | DISP_CS     | 10      | display chip select (active low), J4.2
//  PA19       | DISP_BL     | 11      | display aux/backlight output, J4.1
//  PA20       | LedsB-S     |  9      | Bottom LED section gate -> 470R -> U11
//  PA21       | LedsL-S     |  8      | Left LED section gate  -> 470R -> U10
//  PA22       | McuTX       |  1      | Serial1 TX -> L86 GNSS RX (U4.1)
//  PA23       | McuRX       |  0      | Serial1 RX <- L86 GNSS TX (U4.2)
//  PB02       | I2C_SDA     | 22/SDA  | RV-3028 (0x52), TPA2016 (0x58),
//  PB03       | I2C_SCL     | 23/SCL  | LIS3DH (0x18), nPM1300 (0x6B); 4.7k PU
//  PB08       | LIS3DH_INT1 | 18/A4   | Accelerometer interrupt 1 (U7.11)
//  PB12       | BUTTON3     |  7      | Button 3 (active low, 1M pullup R9)
//  PB13       | BUTTON2     |  4      | Button 2 (active low, 1M pullup R8)
//  PB14       | BUTTON1     |  5      | Button 1 (active low; via U9 buffer,
//             |             |         | input = PMIC SHPHLD)
//  PB15       | BUTTON4     |  6      | Button 4 (active low, 1M pullup R10)
//  PB16       | (unconn.)   |  3      | v2: unconnected (v1: SPEAKER buzzer)
//  PB17       | AmpShutdown |  2      | TPA2016 ~SD (HIGH = amp on, 10k PU R68)
//  PA08..11,  | Flash IO    | QSPI    | U8 tune flash. Supported: W25Q128JV
//  PB10,PB11  |             |         | (3V) or MX25L3233F. NB: first v2
//             |             |         | board has a 1.8V W25Q128FW — wrong
//             |             |         | part, storage disabled (HARDWARE_V2)
//  --- not in the Metro M4 variant: direct PORT access ---
//  PB00       | GNSS_FOn    |  -      | L86 FORCE_ON (U4.7)
//  PB31       | GNSS_Reset  |  -      | L86 RESET_N (U4.10), active low
//  PB01       | (unconn.)   |  -      | v2: unconnected (v1: 24LC512 WP)
//  PA00/PA01  | 32.768 kHz  |  -      | X1 crystal (XOSC32K) — not GPIO
//
// Buttons sit in a row above the display, left to right: SW1 SW2 SW3 SW4.

#pragma once
#include <Arduino.h>

// --- Display (NV3007 428x142 landscape RGB565 TFT, 4-wire SPI on J4) ---
#define PIN_OLED_CS 10
#define PIN_OLED_DC 12
#define PIN_OLED_RST 13
#define PIN_OLED_BL 11

// --- Buttons, left to right as mounted above the display ---
#define PIN_BUTTON1 5 // PB14 (SW1, leftmost)
#define PIN_BUTTON2 4 // PB13 (SW2)
#define PIN_BUTTON3 7 // PB12 (SW3)
#define PIN_BUTTON4 6 // PB15 (SW4, rightmost)

// --- LED sections (gates of low-side MOSFETs, HIGH = section on) ---
// v2: LED anodes fed from +5V (TPS61023 boost) via 100R each (R20-R53);
// each gate has a 470R series resistor + 10k pulldown. (v1 fed from the
// supercap ALARMPOWER rail.)
#define PIN_LEDS_LEFT 8    // PA21, 10 LEDs (LED1-10),  gate R15
#define PIN_LEDS_BOTTOM 9  // PA20, 14 LEDs (LED11-24), gate R54
#define PIN_LEDS_RIGHT A2  // PA06, 10 LEDs (LED25-34), gate R56

// --- Audio ---
#define PIN_AUDIO_DAC PIN_DAC0 // PA02, AC-coupled into TPA2016 right input
#define PIN_AMP_SHUTDOWN 2     // PB17, HIGH = amp on (TPA2016 ~SD, 10k PU R68)
#define PIN_BUZZER 3           // PB16, v2: UNCONNECTED (buzzer removed);
                               // v1 gated J5 load on the supercap rail

// --- Power / status ---
// v2: PA04 is nPM1300 GPIO0 (not a supercap CAPGOOD). Kept as PIN_CAPGOOD
// for v1 source compatibility; on v2 it reads the (unconfigured) PMIC GPIO0.
#define PIN_CAPGOOD A3 // PA04, v2: nPM1300 GPIO0 (v1: LTC3226 CAPGOOD)
#define PIN_ACCEL_INT1 A4 // PB08, LIS3DH INT1

// --- I2C addresses ---
#define I2C_ADDR_RTC 0x52    // RV-3028-C7
#define I2C_ADDR_AMP 0x58    // TPA2016D2
#define I2C_ADDR_EEPROM 0x50 // 24LC512 — v2: NOT FITTED (v1 only)
#define I2C_ADDR_PMIC 0x6B   // nPM1300 PMIC (v2 only)
#define I2C_ADDR_ACCEL 0x18  // LIS3DH; v2 straps SA0 low (R18 10k->GND) => 0x18
                             // by design, but boards have answered at 0x19 too
                             // -> the driver probes both

// --- Pins not present in the Metro M4 variant: direct PORT access ---
// PORTB = PORT->Group[1]
#define GNSS_FON_PORTPIN 0    // PB00, L86 FORCE_ON (leave hi-Z normally)
#define EEPROM_WP_PORTPIN 1   // PB01, v2: UNCONNECTED (v1: 24LC512 WP)
#define GNSS_RESET_PORTPIN 31 // PB31, L86 RESET_N (active low, keep hi-Z)

static inline void portb_output(uint8_t pin, bool level) {
  if (level)
    PORT->Group[1].OUTSET.reg = (1ul << pin);
  else
    PORT->Group[1].OUTCLR.reg = (1ul << pin);
  PORT->Group[1].DIRSET.reg = (1ul << pin);
}

static inline void portb_hiz(uint8_t pin) {
  PORT->Group[1].DIRCLR.reg = (1ul << pin);
  PORT->Group[1].PINCFG[pin].reg = 0; // no pull, input buffer off
}
